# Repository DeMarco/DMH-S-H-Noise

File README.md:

# DMH-S-H-Noise

Implementation of the S&H + Noise Generator circuits by Moritz Klein into Kosmo format.

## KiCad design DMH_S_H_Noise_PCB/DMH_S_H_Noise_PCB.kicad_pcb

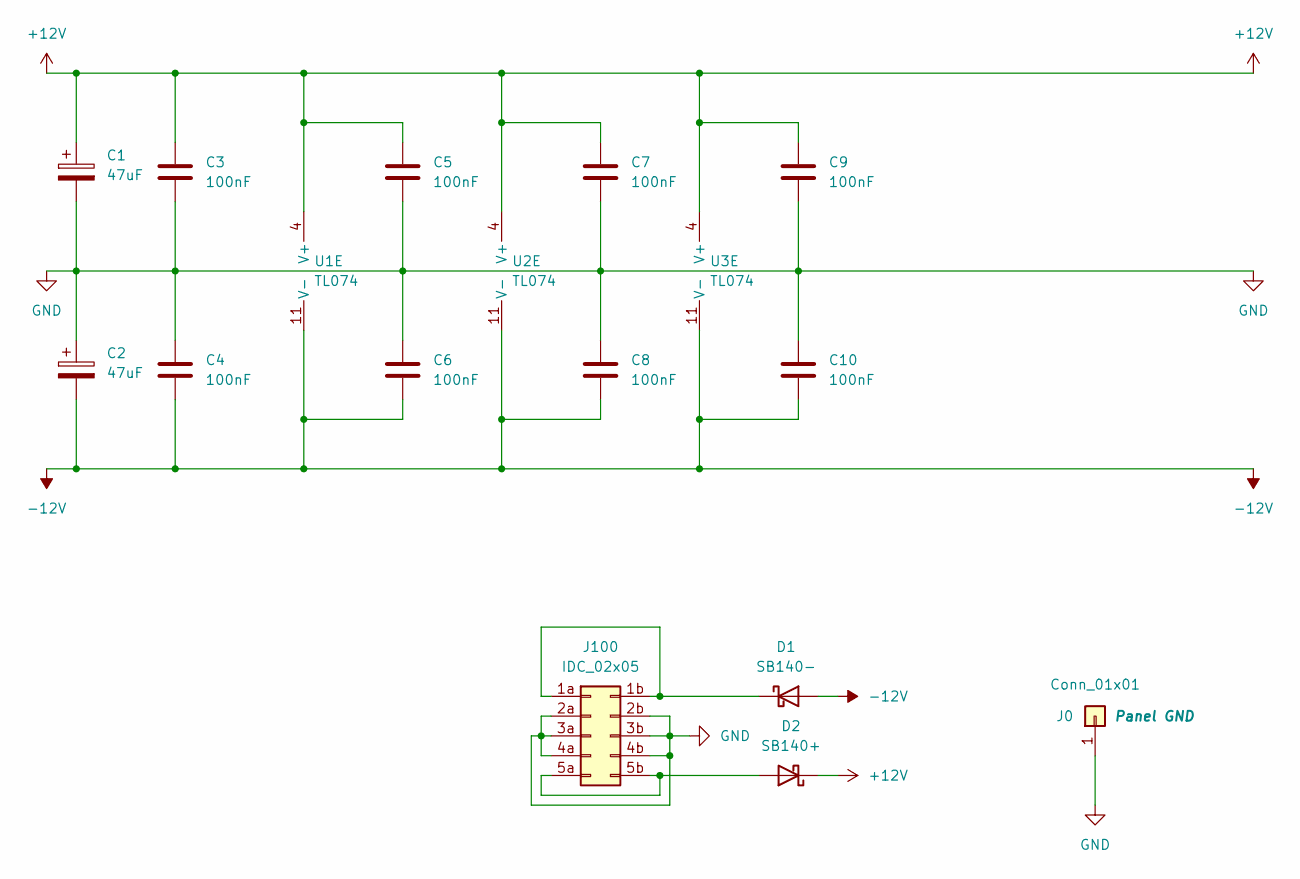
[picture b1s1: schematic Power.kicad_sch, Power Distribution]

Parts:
C1, C2: 47uF; CP_Radial_D5.0mm_P2.00mm
C3, C4, C5, C6, C7, C8, C9, C10: 100nF; C_Disc_D4.3mm_W1.9mm_P5.00mm
D1: SB140-; D_DO-41_SOD81_P10.16mm_Horizontal
D2: SB140+; D_DO-41_SOD81_P10.16mm_Horizontal
J0: Conn_01x01; PinHeader_1x01_P2.54mm_Vertical
J100: IDC_02x05; IDC-Header_2x05_P2.54mm_Vertical_Eurorack
U1, U2, U3: TL074; DIP-14_W7.62mm_Socket

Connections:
+12V: C1.1, C3.1, C5.1, C7.1, C9.1, D2.1 (K), U1.4 (V+), U2.4 (V+), U3.4 (V+); also elsewhere on the board
-12V: C2.2, C4.2, C6.2, C8.2, C10.2, D1.2 (A), U1.11 (V-), U2.11 (V-), U3.11 (V-)
GND: C1.2, C2.1, C3.2, C4.1, C5.2, C6.1, C7.2, C8.1, C9.2, C10.1, J0.1, J100.2a, J100.2b, J100.3a, J100.3b, J100.4a, J100.4b; also elsewhere on the board
unnamed: D1.1 (K), J100.1a, J100.1b
unnamed: D2.2 (A), J100.5a, J100.5b

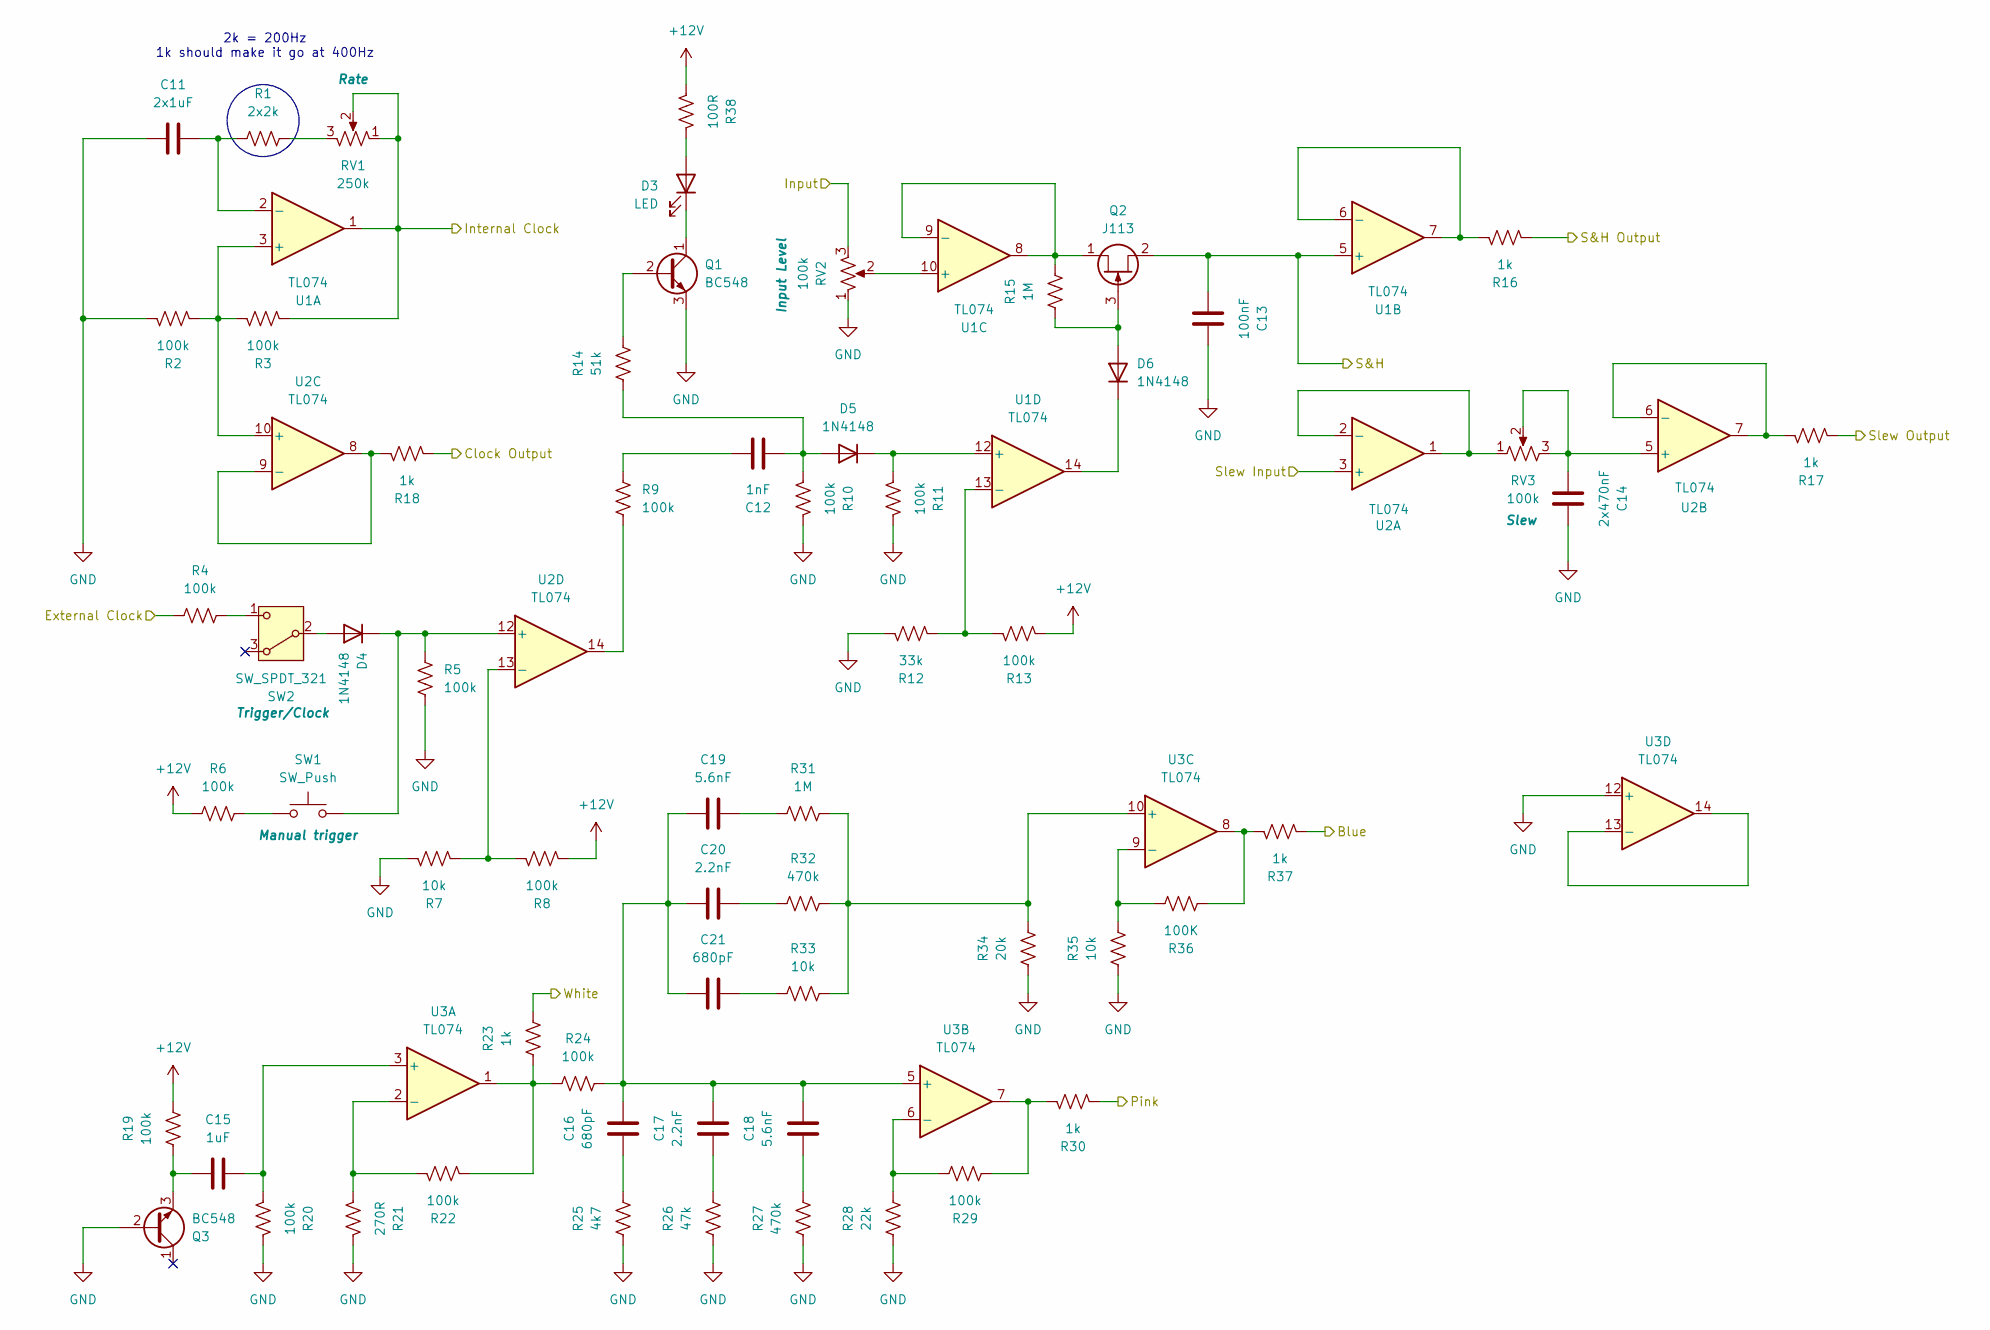
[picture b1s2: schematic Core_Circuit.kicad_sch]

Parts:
C11: 2x1uF; C_Disc_D4.3mm_W1.9mm_P5.00mm
C12: 1nF; C_Disc_D4.3mm_W1.9mm_P5.00mm
C13: 100nF; C_Disc_D4.3mm_W1.9mm_P5.00mm
C14: 2x470nF; C_Disc_D4.3mm_W1.9mm_P5.00mm
C15: 1uF; C_Disc_D4.3mm_W1.9mm_P5.00mm
C16, C21: 680pF; C_Disc_D4.3mm_W1.9mm_P5.00mm
C17, C20: 2.2nF; C_Disc_D4.3mm_W1.9mm_P5.00mm
C18, C19: 5.6nF; C_Disc_D4.3mm_W1.9mm_P5.00mm
D3: LED; LED_D3.0mm
D4, D5, D6: 1N4148; D_DO-35_SOD27_P7.62mm_Horizontal
Q1, Q3: BC548; TO-92_Inline_Wide
Q2: J113; TO-92L_Inline
R1: 2x2k; R_Axial_DIN0207_L6.3mm_D2.5mm_P7.62mm_Horizontal
R2, R3, R4, R5, R6, R8, R9, R10, R11, R13, R19, R20, R22, R24, R29: 100k; R_Axial_DIN0207_L6.3mm_D2.5mm_P7.62mm_Horizontal
R7, R33, R35: 10k; R_Axial_DIN0207_L6.3mm_D2.5mm_P7.62mm_Horizontal
R12: 33k; R_Axial_DIN0207_L6.3mm_D2.5mm_P7.62mm_Horizontal
R14: 51k; R_Axial_DIN0207_L6.3mm_D2.5mm_P7.62mm_Horizontal
R15, R31: 1M; R_Axial_DIN0207_L6.3mm_D2.5mm_P7.62mm_Horizontal
R16, R17, R18, R23, R30, R37: 1k; R_Axial_DIN0207_L6.3mm_D2.5mm_P7.62mm_Horizontal
R21: 270R; R_Axial_DIN0207_L6.3mm_D2.5mm_P7.62mm_Horizontal
R25: 4k7; R_Axial_DIN0207_L6.3mm_D2.5mm_P7.62mm_Horizontal
R26: 47k; R_Axial_DIN0207_L6.3mm_D2.5mm_P7.62mm_Horizontal
R27, R32: 470k; R_Axial_DIN0207_L6.3mm_D2.5mm_P7.62mm_Horizontal
R28: 22k; R_Axial_DIN0207_L6.3mm_D2.5mm_P7.62mm_Horizontal
R34: 20k; R_Axial_DIN0207_L6.3mm_D2.5mm_P7.62mm_Horizontal
R36: 100K; R_Axial_DIN0207_L6.3mm_D2.5mm_P7.62mm_Horizontal
R38: 100R; R_Axial_DIN0207_L6.3mm_D2.5mm_P7.62mm_Horizontal
RV1: 250k; Potentiometer_Alpha_RD901F-40-00D_Single_Vertical
RV2, RV3: 100k; Potentiometer_Alpha_RD901F-40-00D_Single_Vertical
SW1: SW_Push; SW_Cherry_MX_1.00u_PCB
SW2: SW_SPDT_321; Toggle_Switch_THT
U1, U2, U3: TL074; DIP-14_W7.62mm_Socket

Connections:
+12V: R6.2, R8.1, R13.1, R19.1, R38.1; also elsewhere on the board
/Core Circuit/Blue: R37.1; also elsewhere on the board
/Core Circuit/Clock Output: R18.1; also elsewhere on the board
/Core Circuit/External Clock: R4.2; also elsewhere on the board
/Core Circuit/Input: RV2.3; also elsewhere on the board
/Core Circuit/Internal Clock: R3.1, RV1.1, RV1.2, U1.1; also elsewhere on the board
/Core Circuit/Pink: R30.1; also elsewhere on the board
/Core Circuit/S&H: C13.1, Q2.2 (S), U1.5 (+); also elsewhere on the board
/Core Circuit/S&H Output: R16.1; also elsewhere on the board
/Core Circuit/Slew Input: U2.3 (+); also elsewhere on the board
/Core Circuit/Slew Output: R17.1; also elsewhere on the board
/Core Circuit/White: R23.1; also elsewhere on the board
GND: C11.1, C13.2, C14.2, Q1.3 (E), Q3.2 (B), R2.2, R5.1, R7.2, R10.2, R11.2, R12.2, R20.2, R21.2, R25.2, R26.2, R27.2, R28.2, R34.2, R35.2, RV2.1, U3.12 (+); also elsewhere on the board
unnamed: C12.2, R9.2
unnamed: C16.2, R25.1
unnamed: C17.2, R26.1
unnamed: C18.2, R27.1
unnamed: C19.2, R31.2
unnamed: C20.2, R32.2
unnamed: C21.2, R33.2
unnamed: D3.2 (A), R38.2
unnamed: D3.1 (K), Q1.1 (C)
unnamed: D4.2 (A), SW2.2 (B)
unnamed: D4.1 (K), R5.2, SW1.2, U2.12 (+)
unnamed: C12.1, D5.2 (A), R10.1, R14.2
unnamed: D5.1 (K), R11.1, U1.12 (+)
unnamed: D6.2 (A), Q2.3 (G), R15.2
unnamed: D6.1 (K), U1.14
unnamed: Q1.2 (B), R14.1
unnamed: Q2.1 (D), R15.1, U1.8, U1.9 (-)
unnamed: C15.1, Q3.3 (E), R19.2
unnamed: R1.1, RV1.3
unnamed: R6.1, SW1.1
unnamed: R9.1, U2.14
unnamed: R22.1, R23.2, R24.2, U3.1
unnamed: R29.2, R30.2, U3.7
unnamed: R36.2, R37.2, U3.8
unnamed: R4.1, SW2.1 (C)
unnamed: R2.1, R3.2, U1.3 (+), U2.10 (+)
unnamed: C11.2, R1.2, U1.2 (-)
unnamed: R16.2, U1.6 (-), U1.7
unnamed: RV2.2, U1.10 (+)
unnamed: R12.1, R13.2, U1.13 (-)
unnamed: RV3.1, U2.1, U2.2 (-)
unnamed: C14.1, RV3.2, RV3.3, U2.5 (+)
unnamed: R17.2, U2.6 (-), U2.7
unnamed: R18.2, U2.8, U2.9 (-)
unnamed: R7.1, R8.2, U2.13 (-)
unnamed: C15.2, R20.1, U3.3 (+)
unnamed: R21.1, R22.2, U3.2 (-)
unnamed: C16.1, C17.1, C18.1, C19.1, C20.1, C21.1, R24.1, U3.5 (+)
unnamed: R28.1, R29.1, U3.6 (-)
unnamed: R31.1, R32.1, R33.1, R34.1, U3.10 (+)
unnamed: R35.1, R36.1, U3.9 (-)
unnamed: U3.13 (-), U3.14

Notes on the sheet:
2k = 200Hz 1k should make it go at 400Hz

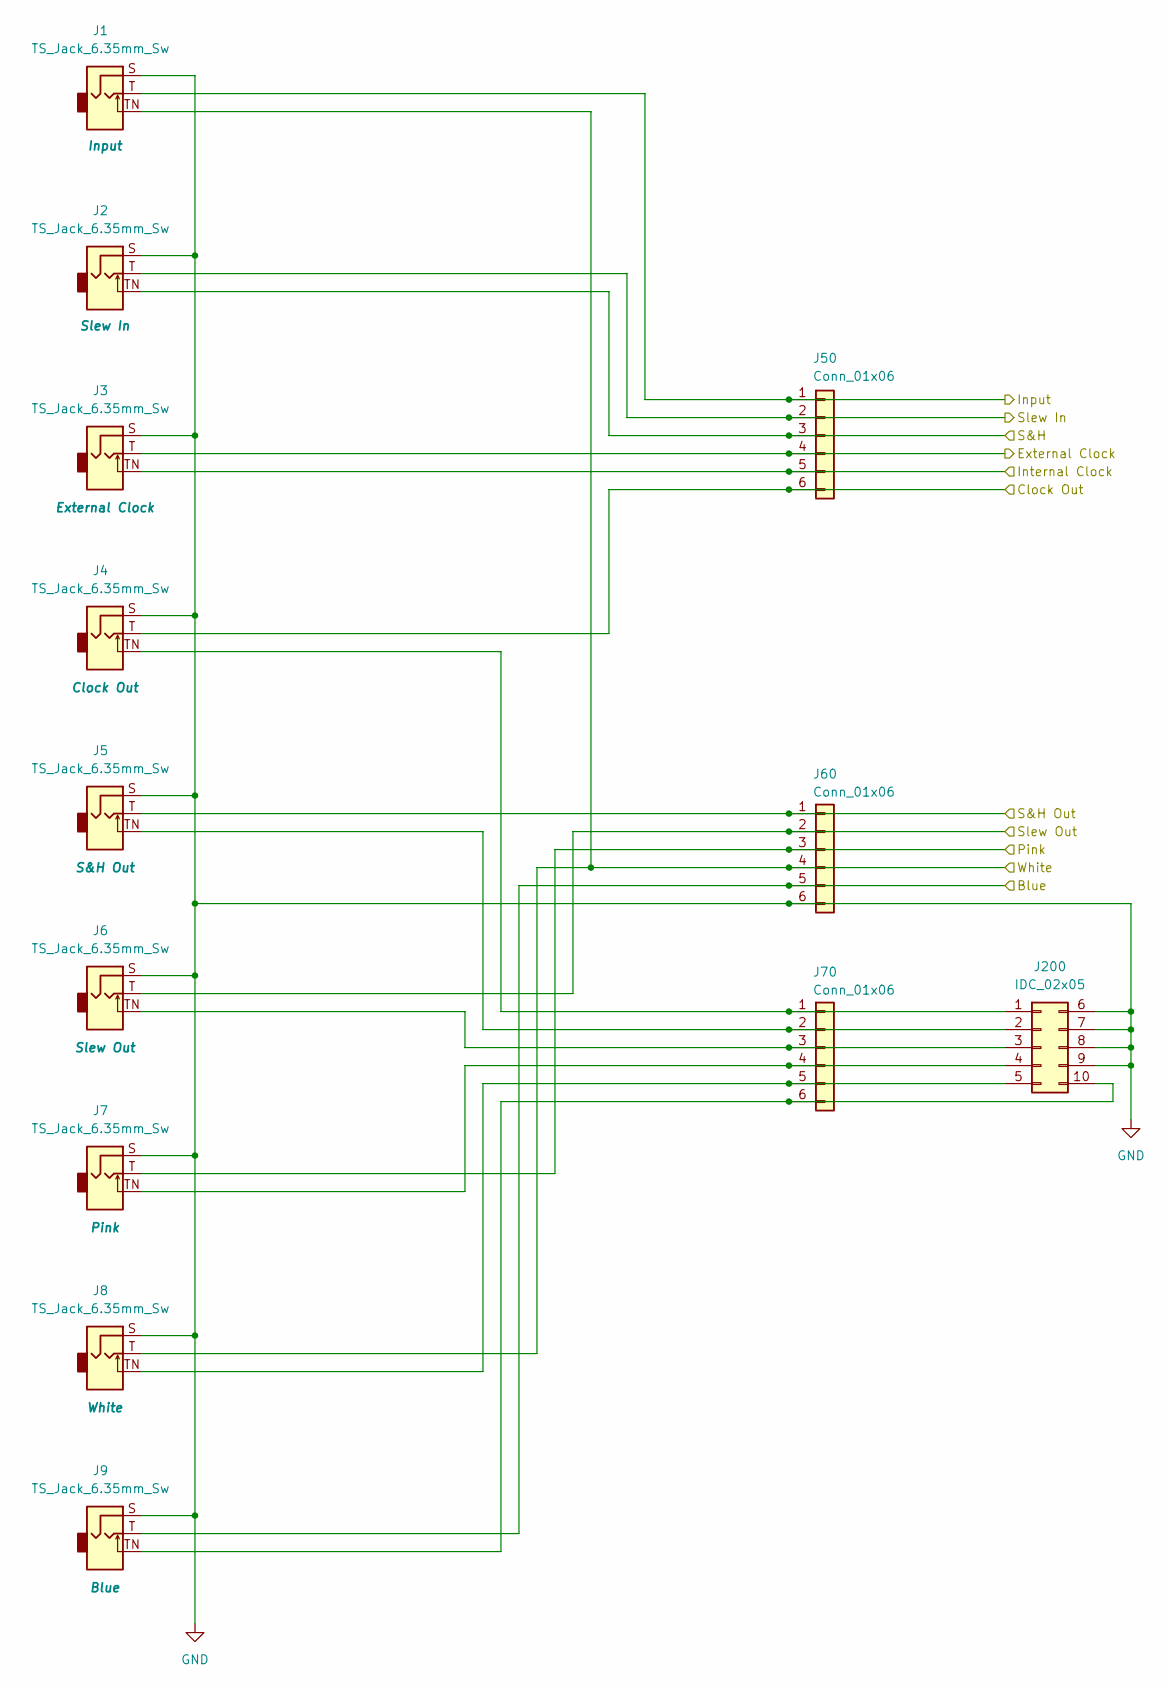
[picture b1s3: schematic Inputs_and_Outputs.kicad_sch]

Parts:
J1, J2, J3, J4, J5, J6, J7, J8, J9: TS_Jack_6.35mm_Sw; CUI_MJ-63052A
J50, J60, J70: Conn_01x06; PinSocket_1x06_P2.54mm_Vertical
J200: IDC_02x05; IDC-Header_2x05_P2.54mm_Vertical_BackBone

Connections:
/Core Circuit/Blue: J9.T, J60.5; also elsewhere on the board
/Core Circuit/Clock Output: J4.T, J50.6; also elsewhere on the board
/Core Circuit/External Clock: J3.T, J50.4; also elsewhere on the board
/Core Circuit/Input: J1.T, J50.1; also elsewhere on the board
/Core Circuit/Internal Clock: J3.TN, J50.5; also elsewhere on the board
/Core Circuit/Pink: J7.T, J60.3; also elsewhere on the board
/Core Circuit/S&H: J2.TN, J50.3; also elsewhere on the board
/Core Circuit/S&H Output: J5.T, J60.1; also elsewhere on the board
/Core Circuit/Slew Input: J2.T, J50.2; also elsewhere on the board
/Core Circuit/Slew Output: J6.T, J60.2; also elsewhere on the board
/Core Circuit/White: J1.TN, J8.T, J60.4; also elsewhere on the board
GND: J1.S, J2.S, J3.S, J4.S, J5.S, J6.S, J7.S, J8.S, J9.S, J60.6, J200.6, J200.7, J200.8, J200.9; also elsewhere on the board
unnamed: J4.TN, J70.1, J200.1
unnamed: J5.TN, J70.2, J200.2
unnamed: J6.TN, J70.3, J200.3
unnamed: J7.TN, J70.4, J200.4
unnamed: J8.TN, J70.5, J200.5
unnamed: J9.TN, J70.6, J200.10

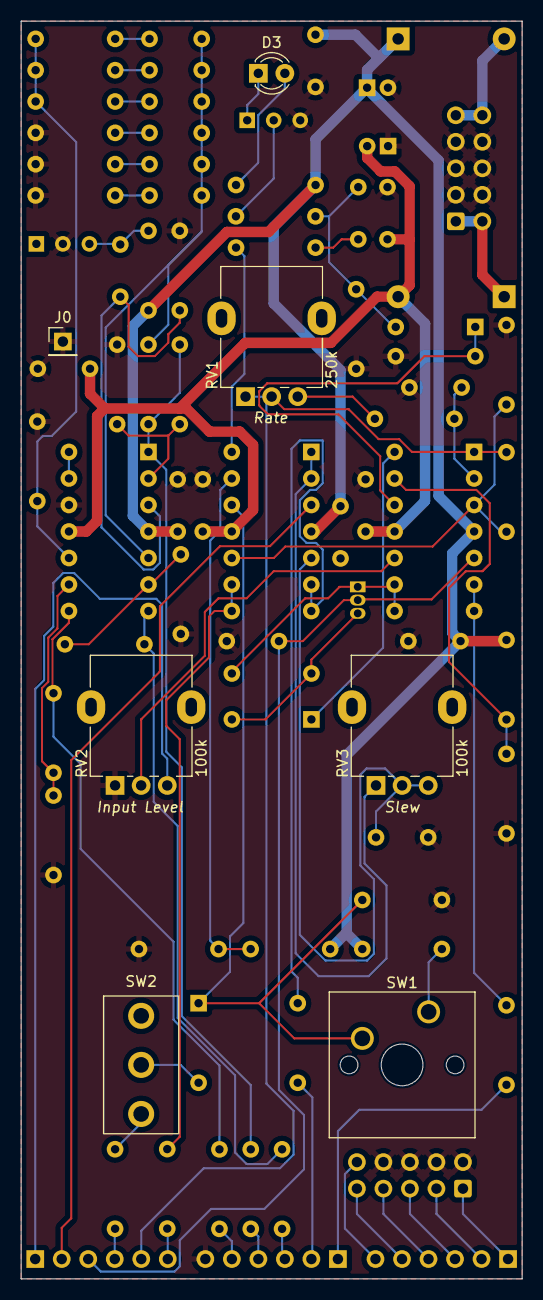
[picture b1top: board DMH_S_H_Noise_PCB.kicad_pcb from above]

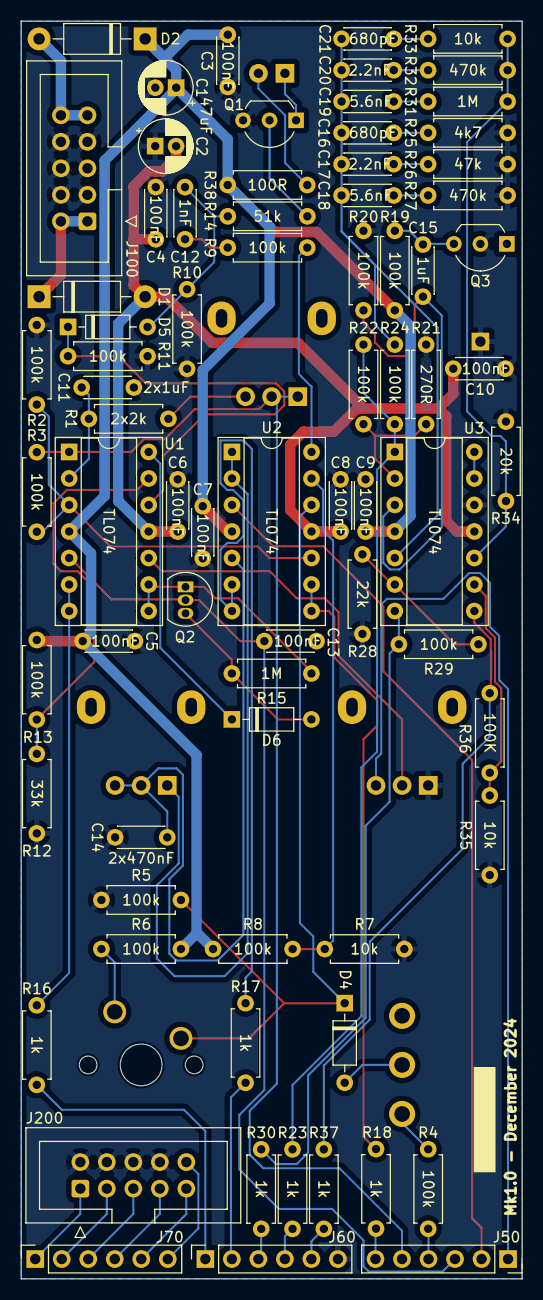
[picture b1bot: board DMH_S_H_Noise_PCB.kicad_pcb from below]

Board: 2 copper layers, 48.0 x 120.5 mm, 82 parts (75 on the bottom side), 64 nets.

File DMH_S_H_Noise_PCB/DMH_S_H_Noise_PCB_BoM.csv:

"Reference","Value","Footprint","Qty"
"C1,C2","47uF","Capacitor_THT:CP_Radial_D5.0mm_P2.00mm","2"
"C3,C4,C5,C6,C7,C8,C9,C10,C13","100nF","Capacitor_THT:C_Disc_D4.3mm_W1.9mm_P5.00mm","9"
"C11","2x1uF","Capacitor_THT:C_Disc_D4.3mm_W1.9mm_P5.00mm","1"
"C12","1nF","Capacitor_THT:C_Disc_D4.3mm_W1.9mm_P5.00mm","1"
"C14","2x470nF","Capacitor_THT:C_Disc_D4.3mm_W1.9mm_P5.00mm","1"
"C15","1uF","Capacitor_THT:C_Disc_D4.3mm_W1.9mm_P5.00mm","1"
"C16,C21","680pF","Capacitor_THT:C_Disc_D4.3mm_W1.9mm_P5.00mm","2"
"C17,C20","2.2nF","Capacitor_THT:C_Disc_D4.3mm_W1.9mm_P5.00mm","2"
"C18,C19","5.6nF","Capacitor_THT:C_Disc_D4.3mm_W1.9mm_P5.00mm","2"
"D1","SB140-","Diode_THT:D_DO-41_SOD81_P10.16mm_Horizontal","1"
"D2","SB140+","Diode_THT:D_DO-41_SOD81_P10.16mm_Horizontal","1"
"D3","LED","LED_THT:LED_D3.0mm","1"
"D4,D5,D6","1N4148","Diode_THT:D_DO-35_SOD27_P7.62mm_Horizontal","3"
"J0","Conn_01x01","Connector_PinHeader_2.54mm:PinHeader_1x01_P2.54mm_Vertical","1"
"J1,J2,J3,J4,J5,J6,J7,J8,J9","TS_Jack_6.35mm_Sw","SynthStuff:CUI_MJ-63052A","9"
"J50,J60,J70","Conn_01x06","Connector_PinSocket_2.54mm:PinSocket_1x06_P2.54mm_Vertical","3"
"J100","IDC_02x05","SynthStuff:IDC-Header_2x05_P2.54mm_Vertical_Eurorack","1"
"J200","IDC_02x05","SynthStuff:IDC-Header_2x05_P2.54mm_Vertical_BackBone","1"
"Q1,Q3","BC548","Package_TO_SOT_THT:TO-92_Inline_Wide","2"
"Q2","J113","Package_TO_SOT_THT:TO-92L_Inline","1"
"R1","2x2k","Resistor_THT:R_Axial_DIN0207_L6.3mm_D2.5mm_P7.62mm_Horizontal","1"
"R2,R3,R4,R5,R6,R8,R9,R10,R11,R13,R19,R20,R22,R24,R29","100k","Resistor_THT:R_Axial_DIN0207_L6.3mm_D2.5mm_P7.62mm_Horizontal","15"
"R7,R33,R35","10k","Resistor_THT:R_Axial_DIN0207_L6.3mm_D2.5mm_P7.62mm_Horizontal","3"
"R12","33k","Resistor_THT:R_Axial_DIN0207_L6.3mm_D2.5mm_P7.62mm_Horizontal","1"
"R14","51k","Resistor_THT:R_Axial_DIN0207_L6.3mm_D2.5mm_P7.62mm_Horizontal","1"
"R15,R31","1M","Resistor_THT:R_Axial_DIN0207_L6.3mm_D2.5mm_P7.62mm_Horizontal","2"
"R16,R17,R18,R23,R30,R37","1k","Resistor_THT:R_Axial_DIN0207_L6.3mm_D2.5mm_P7.62mm_Horizontal","6"
"R21","270R","Resistor_THT:R_Axial_DIN0207_L6.3mm_D2.5mm_P7.62mm_Horizontal","1"
"R25","4k7","Resistor_THT:R_Axial_DIN0207_L6.3mm_D2.5mm_P7.62mm_Horizontal","1"
"R26","47k","Resistor_THT:R_Axial_DIN0207_L6.3mm_D2.5mm_P7.62mm_Horizontal","1"
"R27,R32","470k","Resistor_THT:R_Axial_DIN0207_L6.3mm_D2.5mm_P7.62mm_Horizontal","2"
"R28","22k","Resistor_THT:R_Axial_DIN0207_L6.3mm_D2.5mm_P7.62mm_Horizontal","1"
"R34","20k","Resistor_THT:R_Axial_DIN0207_L6.3mm_D2.5mm_P7.62mm_Horizontal","1"
"R36","100K","Resistor_THT:R_Axial_DIN0207_L6.3mm_D2.5mm_P7.62mm_Horizontal","1"
"R38","100R","Resistor_THT:R_Axial_DIN0207_L6.3mm_D2.5mm_P7.62mm_Horizontal","1"
"RV1","250k","SynthStuff:Potentiometer_Alpha_RD901F-40-00D_Single_Vertical","1"
"RV2,RV3","100k","SynthStuff:Potentiometer_Alpha_RD901F-40-00D_Single_Vertical","2"
"SW1","SW_Push","SynthStuff:SW_Cherry_MX_1.00u_PCB","1"
"SW2","SW_SPDT_321","SynthStuff:Toggle_Switch_THT","1"
"U1,U2,U3","TL074","Package_DIP:DIP-14_W7.62mm_Socket","3"

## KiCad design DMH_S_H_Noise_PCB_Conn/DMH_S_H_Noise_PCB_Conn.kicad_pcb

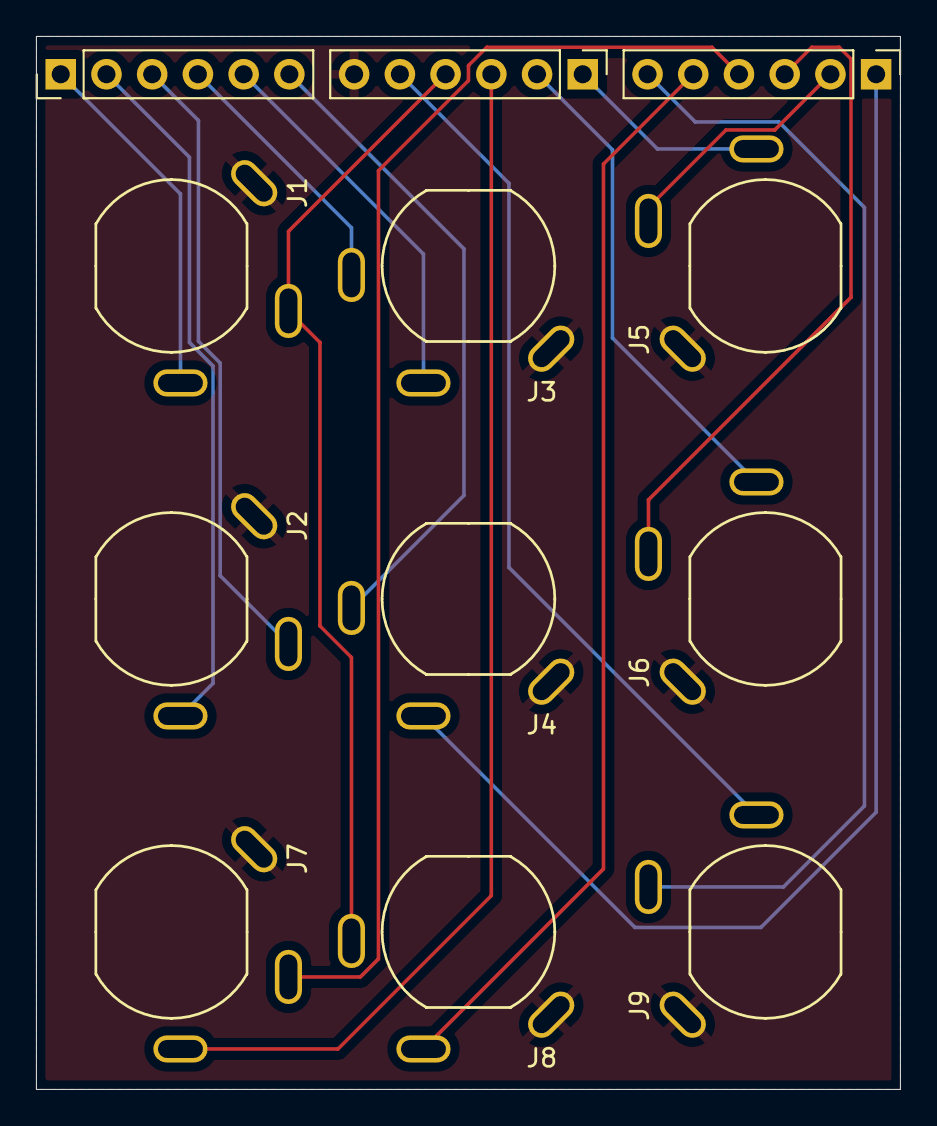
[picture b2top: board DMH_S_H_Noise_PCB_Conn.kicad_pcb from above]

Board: 2 copper layers, 48.0 x 58.5 mm, 12 parts (0 on the bottom side), 18 nets.

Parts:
J1, J2, J3, J4, J5, J6, J7, J8, J9: TS_Jack_6.35mm_Sw; CUI_MJ-63052A
J50, J60, J70: Conn_01x06; PinHeader_1x06_P2.54mm_Vertical

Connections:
/Inputs and Outputs/Blue: J9.T, J60.5
/Inputs and Outputs/Clock Out: J4.T, J50.6
/Inputs and Outputs/External Clock: J3.T, J50.4
/Inputs and Outputs/Input: J1.T, J50.1
/Inputs and Outputs/Internal Clock: J3.TN, J50.5
/Inputs and Outputs/Pink: J7.T, J60.3
/Inputs and Outputs/S&H: J2.TN, J50.3
/Inputs and Outputs/S&H Out: J5.T, J60.1
/Inputs and Outputs/Slew In: J2.T, J50.2
/Inputs and Outputs/Slew Out: J6.T, J60.2
/Inputs and Outputs/White: J1.TN, J8.T, J60.4
GND: J1.S, J2.S, J3.S, J4.S, J5.S, J6.S, J7.S, J8.S, J9.S, J60.6
unnamed: J4.TN, J70.1
unnamed: J5.TN, J70.2
unnamed: J6.TN, J70.3
unnamed: J7.TN, J70.4
unnamed: J8.TN, J70.5
unnamed: J9.TN, J70.6

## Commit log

2024-11-01 Prepared KiCad projects
2024-11-01 Created front panel
2024-11-01 Started schematic
2024-11-02 Designed S&h circuit
2024-11-03 Completed circuit
2024-11-03 Corrections during breadboard assembly
2024-11-05 Updated resistor values after test
2024-11-08 Added Rate LED to the panel
2024-11-08 Manual trigger panel experiments ongoing
2024-11-09 Added toggle switch for trigger source
2024-11-09 Finished front panel
2024-11-10 Finished schematic
2024-11-10 Added toggle switch to schematic
2024-11-12 Added clock output
2024-11-14 Component placement ongoing
2024-11-15 Finished placement and initial routing
2024-11-17 Restarted positioning from scratch
2024-11-17 Minor positioning corrections
2024-11-17 Rerouting finished
2024-11-17 Sync libs
2024-11-18 Minor corrections
2024-11-18 Finished connectors PCB
2024-11-26 Update SynthStuff
2024-12-04 Generated Gerbers
2024-12-08 Generated BoM
2025-05-07 Exported BoM
2025-08-01 Uploaded BoM
